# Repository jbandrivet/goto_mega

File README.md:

# GotoAndrivet — Contrôleur Multi-Montures OnStep

**Site du projet : [goto-andrivet.duckdns.org](https://goto-andrivet.duckdns.org)**

Ce projet supporte de manière universelle trois types de montures astronomiques :
1. **Alt-Azimutale (AltAz)** : Pour montures Dobson et Alt-Azimutales standards.
2. **Fourche Équatoriale (ForkEq)** : Pour montures équatoriales à fourche ou tables équatoriales (aucun retournement de méridien requis, suivi sidéral direct sur l'angle horaire).
3. **Monture Équatoriale Allemande (GermanEq / GEM)** : Pour montures équatoriales allemandes (gestion automatique du **retournement de méridien** et de la position de pilier *Pier Side* Est/Ouest).

---

## Installation en un clic (Linux)

La carte du ciel et GoTo (**GotoAndrivet**) et le **configurateur** s'installent ensemble, avec leurs raccourcis sur le Bureau et dans le menu des applications. L'installateur prend toujours la dernière version du dépôt ; ensuite, le bouton « Mise à jour » des applications suffit.

**Ubuntu et Debian, le plus simple : [⬇ Télécharger GotoAndrivet.deb](https://github.com/jbandrivet/goto_mega/releases/latest/download/GotoAndrivet.deb)**

1. Double-cliquez sur le fichier téléchargé : le Centre d'applications s'ouvre. Cliquez sur **Installer** (votre mot de passe est demandé).
2. Ouvrez **GotoAndrivet - Carte du ciel** depuis le menu des applications. La première fois, GotoAndrivet s'installe dans votre dossier personnel (quelques minutes), puis s'ouvre.

**Autres distributions : [⬇ Télécharger l'installateur Linux](https://github.com/jbandrivet/goto_mega/releases/latest/download/Install_Goto_Universal)**, puis, dans le dossier Téléchargements :

1. clic droit sur `Install_Goto_Universal` → **Propriétés** → activez **Exécutable comme programme** ;
2. clic droit → **Exécuter comme un programme**, puis « Installer ».

Le double-clic ne lance pas un programme téléchargé : il propose de chercher une application dans le Centre d'applications, qui ne trouve rien. Passez par le clic droit.

Ou en une seule commande, dans un terminal :

```sh
wget -qO- https://raw.githubusercontent.com/jbandrivet/goto_mega/main/installer.sh | sh
```

Prérequis pour l'installateur et la commande (le paquet .deb les installe tout seul) : `sudo apt install python3-venv python3-tk`. Pour le module caméra : `sudo apt install astrometry.net astrometry-data-tycho2` et le SDK caméra de ZWO.

---

## Structure du Projet

* **`goto_andrivet.py`** : L'application principale en Python (interface graphique Tkinter avec carte du ciel interactive : étoiles, constellations, Soleil, Lune et planètes, catalogues Messier/NGC/IC/Caldwell, dérotateur et mise à jour en ligne).
* **`photo.py`** : Le module caméra de la carte du ciel (caméra ZWO ou simulée, photos FITS, astrométrie locale avec solve-field, correction après GoTo, modèle de pointage, angle de cadrage).
* **`guidage.py`** : Le module de guidage de la carte du ciel (deuxième caméra ZWO ou simulée, calibration automatique, corrections envoyées par le PC à la monture, courbe des erreurs, dithering entre les poses).
* **`goto_andrivet_config_tool.py`** : L'utilitaire de configuration en style Windows 95 permettant de régler les coordonnées, vitesses, rapports d'engrenage et de flasher le firmware.
* **`raquette_virtuelle.py`** : L'émulateur de la raquette Teensy pour piloter le télescope depuis l'ordinateur.
* **`ciel_donnees.py`** : Les données de la carte du ciel : étoiles du Yale Bright Star Catalogue jusqu'à la magnitude 6,5, lignes et noms des 88 constellations (Stellarium, CC BY-SA 4.0), objets Messier, Caldwell, NGC et IC (OpenNGC, CC BY-SA 4.0). Fichier généré par `outils/generer_ciel_donnees.py` : ne pas le modifier à la main.
* **`mise_a_jour.py`** : La mise à jour en ligne depuis GitHub, commune à la carte du ciel et à l'utilitaire de configuration.
* **`outils/`** : Le générateur de `ciel_donnees.py` (il télécharge les catalogues auprès du CDS, de Stellarium et d'OpenNGC).
* **`mega_monture/`** : Le firmware classique (1 étoile) pour le contrôleur Arduino Mega 2560.
* **`teensy_monture/`** : Le nouveau firmware haute performance pour contrôleur Teensy 4.1 (Inclut le Modèle de Pointage N-Étoiles par interpolation IDW).
* **`teensy_raquette/`** : Le firmware C++ pour la raquette physique avec écran LCD (sur Teensy 4.1).

---

## Guide d'Installation & Mode d'Emploi

### 1. Prérequis
Pour exécuter les applications graphiques en Python sur votre ordinateur, vous devez disposer de **Python 3**, du module **Tkinter** et de la bibliothèque **pyserial**. La bibliothèque **ephem** est facultative : elle affiche le Soleil, la Lune et les planètes sur la carte du ciel.

Sur Ubuntu / Debian / Raspberry Pi OS, installez-les via votre terminal :
```bash
sudo apt update
sudo apt install python3 python3-tk python3-pip
pip3 install pyserial ephem
```

### 2. Démarrage des Applications
Exécutez les scripts Python correspondants depuis le dossier du projet :

* **Configuration & Flashage** :
  ```bash
  python3 goto_andrivet_config_tool.py
  ```
* **Cartographie du Ciel & Pilotage** :
  ```bash
  python3 goto_andrivet.py
  ```
* **Raquette Virtuelle (Émulateur)** :
  ```bash
  python3 raquette_virtuelle.py
  ```

### 3. Compiler & Flasher sans IDE Arduino
Vous pouvez programmer vos cartes directement depuis l'utilitaire de configuration (sans avoir besoin d'ouvrir l'IDE Arduino classique) :
1. Installez l'utilitaire [arduino-cli](https://arduino.github.io/arduino-cli/latest/) sur votre PC.
2. Ouvrez l'utilitaire de configuration (`python3 goto_andrivet_config_tool.py`).
3. Sélectionnez le **Port** série de votre carte dans les paramètres de connexion.
4. Dans l'encadré **« Téléversement du Firmware »**, cliquez sur le bouton correspondant à votre carte pour compiler et flasher automatiquement.

### 4. Schéma de Câblage Rapide (Monture : Mega ou Teensy)

Câblez votre contrôleur principal en suivant ce schéma (les broches sont identiques pour le Mega et le Teensy, à l'exception du Buzzer, de l'`ENB` du focuseur et du GPS, dont les fils TX/RX sont croisés d'une carte à l'autre) :

| Composant / Axe | Broche Arduino Mega 2560 | Broche Teensy 4.1 | Signal Module / Driver |
| :--- | :--- | :--- | :--- |
| **Moteur Azimut (AZ/RA)** | **Pin 2** | **Pin 2** | `PUL+` (Pulse/Step) |
| | **Pin 3** | **Pin 3** | `DIR+` (Direction) |
| | **Pin 4** | **Pin 4** | `ENB+` (Enable) |
| **Moteur Altitude (ALT/DEC)** | **Pin 5** | **Pin 5** | `PUL+` (Pulse/Step) |
| | **Pin 6** | **Pin 6** | `DIR+` (Direction) |
| | **Pin 7** | **Pin 7** | `ENB+` (Enable) |
| **Moteur Dérotateur** | **Pin 8** | **Pin 8** | `PUL+` (Pulse/Step) |
| | **Pin 9** | **Pin 9** | `DIR+` (Direction) |
| | **Pin 10** | **Pin 10** | `ENB+` (Enable) |
| **Moteur Focuseur** | **Pin 11** | **Pin 11** | `PUL+` (Pulse/Step) |
| | **Pin 12** | **Pin 12** | `DIR+` (Direction) |
| | **Pin 13** | **Pin 21** | `ENB+` (Enable) |
| **Buzzer** | **Pin 49** | **Pin 20** | Mega : borne `+` en direct (buzzer actif). Teensy : par un transistor (voir § 6) |
| **Port Série PC** | **Non dispo** | **Pin 25 (RX6)** | `TX` de l'adaptateur USB/Série TTL (Câble long) |
| | **Non dispo** | **Pin 24 (TX6)** | `RX` de l'adaptateur USB/Série TTL |
| **Raquette Teensy** | **Pin 15 (RX3)** | **Pin 15 (RX3)** | `TX` de la raquette Teensy |
| | **Pin 14 (TX3)** | **Pin 14 (TX3)** | `RX` de la raquette Teensy |
| **Module GPS** | **Pin 17 (RX2)** | **Pin 16 (RX4)** | `TX` du module GPS |
| | **Pin 16 (TX2)** | **Pin 17 (TX4)** | `RX` du module GPS |
| **Drivers TMC5160 (SPI1, PCB)** | **Non dispo** | **Pin 26 (MOSI1)** | `SDI` des modules (ponts SPI fermés) |
| | **Non dispo** | **Pin 27 (SCK1)** | `SCK` des modules |
| | **Non dispo** | **Pin 39 (MISO1)** | `SDO` des modules |
| | **Non dispo** | **Pins 41 / 40 / 38 / 37** | `CSN` AZ / ALT / Dérotateur / Focuseur |

*Note : Les signaux de masse négatifs (`PUL-`, `DIR-`, `ENB-` des drivers, GND du buzzer, du GPS et de la Teensy) doivent tous être connectés à une broche **GND** de votre carte.*
*(Consultez le fichier `fiche_technique.md` pour des explications approfondies).*

### 4.1 Schéma de Câblage de la Raquette (Teensy 4.1)

Si vous fabriquez la raquette physique avec un Teensy 4.1, voici le câblage à effectuer :

| Composant | Broche Teensy 4.1 | Connexion / Signal |
| :--- | :--- | :--- |
| **Écran LCD (I2C)** | **Pin 18 (SDA0)** | `SDA` de l'écran LCD |
| | **Pin 19 (SCL0)** | `SCL` de l'écran LCD |
| | **VIN** | `VCC` (5V) de l'écran LCD |
| | **GND** | `GND` de l'écran LCD |
| **Boutons Poussoirs** | **Pin 6** | Bouton **Haut (UP)** (vers GND) |
| | **Pin 7** | Bouton **Bas (DOWN)** (vers GND) |
| | **Pin 8** | Bouton **Gauche (LEFT)** (vers GND) |
| | **Pin 9** | Bouton **Droite (RIGHT)** (vers GND) |
| | **Pin 10** | Bouton **Validation (ENTER)** (vers GND) |
| **Câble RJ11 (vers Mega)**| **GND** | Pin 1 RJ11 (`GND` de la Monture) |
| | **VIN** | Pin 2 RJ11 (`VIN` / `5V` de la Monture) |
| | **Pin 1 (TX1)** | Pin 3 RJ11 (vers `RX3` Pin 15 Monture) |
| | **Pin 0 (RX1)** | Pin 4 RJ11 (vers `TX3` Pin 14 Monture) |

*ATTENTION : Le Teensy est alimenté par la pin 5V du Mega via VIN. Ne pas brancher l'USB du Teensy en même temps, sauf si le pad VUSB a été coupé au préalable.*

### 5. Arduino Mega 2560 vs Teensy 4.1 (Contrôleur de Monture)

Le projet vous permet de choisir le cerveau principal de la monture. Bien que le câblage soit quasiment identique, voici les différences pour vous aider à choisir :

| Caractéristique | Arduino Mega 2560 | Teensy 4.1 |
| :--- | :--- | :--- |
| **Vitesse de calcul** | 16 MHz (8-bit) | **600 MHz** (32-bit ARM) |
| **Précision (Maths)** | Flottants 32-bit lents | **Flottants 64-bit (double)** natifs ultra-rapides |
| **Microstepping & Vitesse max**| Limité (saturera à très haut microstepping) | **Parfait** (génère des impulsions à plus de 200kHz sans sourciller) |
| **Modèle de pointage** | Basique | **N-Étoiles** (50 points mémorisés avec calculs IDW) |
| **Evolutivité (Futur)** | Faible | **Très haute** (Port USB Host pour Manette/Gamepad) |
| **Coût** | ~15-20€ (Clones pas chers) | ~35-40€ |

**Recommandation** : Si vous utilisez de petits drivers (1/16 ou 1/32 de pas) et voulez un système économique, le **Mega 2560** fait parfaitement le travail. Si vous utilisez des drivers modernes (TMC2209, M542) à fort microstepping (1/128, 1/256), que vous voulez des déplacements GoTo ultra-rapides et silencieux, et le modèle de pointage multi-étoiles intégré, optez sans hésiter pour le **Teensy 4.1**.

### 6. Matériel Compatible

Pour monter votre système GotoAndrivet, les composants matériels suivants sont compatibles et recommandés :

* **Cartes de Contrôle** :
  * **Arduino Mega 2560** ou **Teensy 4.1** (au choix pour la carte principale de la monture).
  * **Teensy 4.1** (pour la raquette de commande physique - *Optionnelle*).
* **Drivers de Moteurs** :
  * Drivers standard acceptant des entrées `PUL/DIR` (Impulsion/Direction) comme les modèles **M542**, **DM542**, **TB6600**, **TMC2209**, etc.
  * Deux PCB monture (Teensy) au choix : une carte à modules StepStick, dont le **BTT TMC5160 Pro** configuré en SPI, et une carte pour drivers externes (voir *Cartes Monture* plus bas).
* **Moteurs** :
  * Moteurs pas à pas bipolaires (ex. **NEMA 17** ou **NEMA 23** en 200 pas/tour).
* **Module GPS (Optionnel)** :
  * Module **Adafruit Ultimate GPS** (MTK3339) ou tout autre récepteur GPS délivrant des trames NMEA standards à 9600 bauds sur port série.
* **Afficheur Raquette** :
  * Écran **LCD 20x4** caractères équipé d'un adaptateur **I2C** (généralement à l'adresse `0x27`).
* **Boutons Raquette** :
  * 5 boutons poussoirs momentanés (Haut, Bas, Gauche, Droite, Validation).
* **Alerte Sonore** :
  * Un **Buzzer actif 5V** ou un **Buzzer passif**. Sur le Mega, un buzzer actif se câble directement. Sur le Teensy, passez par un transistor : une broche ne fournit que quelques mA, et un buzzer passif en tire 80 à 200. Un NPN (PN2222A) avec 1 kΩ sur la base, le buzzer entre le 5V et le collecteur, en série avec 68 Ω, et une diode 1N4148 à ses bornes : c'est le montage des cartes.

*Note concernant la raquette physique : La construction de la raquette matérielle (carte Teensy, écran LCD et boutons) n'est **pas obligatoire**. Si vous utilisez la monture en mode "remote", ou que vous la pilotez exclusivement depuis un PC, un planétarium, ou un boîtier type ASIAIR, l'Arduino Mega suffit à lui seul pour tout gérer via la connexion USB.*

---

## Fonctionnalités Avancées

* **Modèle de Pointage N-Étoiles (Teensy Monture uniquement)** : Interpolation des erreurs de suivi et de pointage par IDW (Inverse Distance Weighting) jusqu'à 50 étoiles mémorisées. Support de la commande de remise à zéro `:CML#`.
* **Ajout du type de monture `GermanEq`** : Le firmware de l'Arduino Mega calcule automatiquement les inversions d'axes (Ascension Droite et Déclinaison) lors du franchissement du méridien.
* **Commande standard `:Gm#` implémentée** : Renvoie le *Pier Side* (`E#` pour l'Est, `W#` pour l'Ouest, `N#` pour les autres modes) requis pour les logiciels de guidage comme Ekos/INDI.
* **Commande standard `:D#` implémentée** : Permet l'interrogation dynamique du statut de pointage (Slewing), accélérant drastiquement le modèle de pointage automatique ZWO en évitant les pauses fixes.
* **Intégration complète dans les interfaces** : Le sélecteur de monture dans `goto_andrivet_config_tool.py`, `goto_andrivet.py` et la raquette physique Teensy supporte désormais les trois options distinctes (`AltAz`, `ForkEq`, `GermanEq`).

---

## Licence

Ce projet est sous licence **GNU GPL v3**. Consultez le fichier [LICENSE](LICENSE) pour plus de détails.

## Cartes Monture (PCB 36V / 12V)

Il existe deux cartes monture, au choix selon les drivers utilisés. Elles ont les mêmes dimensions (150 × 110 mm), les mêmes fixations, les mêmes connecteurs d'alimentation, de raquette, de GPS et de PC, et le même câblage du Teensy : le firmware est identique.

| Carte | Dossier | Drivers | Boîtier |
|---|---|---|---|
| **StepStick** | `pcb/monture/` | 4 modules au format StepStick sur la carte (A4988, DRV8825, TMC2208/2209, TMC5160 en SPI) | `boitier_monture.scad`, 45 mm de haut |
| **Drivers externes** | `pcb/monture_ext/` | 4 drivers externes (DM542, DM556, TB6600…), signaux 5 V et alimentation par axe | `boitier_monture_ext.scad`, 35 mm de haut |

Sans PCB, câblez vous-même le Mega ou le Teensy en suivant le plan de câblage de la section 4. Dans l'outil de configuration, indiquez votre choix sur la ligne **« Câblage monture »** (PCB StepStick, PCB drivers externes ou câblage manuel). Avec un PCB, l'outil impose le Teensy 4.1, et la section TMC5160 n'est active qu'avec la carte StepStick. Le bouton **« Plan de câblage »** affiche les broches de la carte choisie et les connecteurs du PCB.

### Commun aux deux cartes
- **Alimentation** : un seul bus moteur, alimenté soit par le **bornier 36V**, soit par la **prise jack 12V**. Chaque entrée passe par une des deux diodes Schottky de `D_IN` (MBR20100CT, cathode commune) : des fils inversés ou un jack à centre négatif ne passent pas, et le 36V du bornier ne remonte pas dans le bloc 12V. Vient ensuite le fusible `F_IN` (TR5 temporisé 4 A, sur support), commun aux deux entrées. Toute la carte et tous les drivers reçoivent la tension de l'entrée branchée, moins environ 0,5 V.
  - En 36V, n'utilisez pas d'A4988 (35 V max) ni de TMC2208/TMC2209 (29 V max) : pour ces petits drivers, alimentez la carte uniquement par le jack 12V.
- Le buck LM2596HV (jusqu'à 60 V en entrée) fabrique le 5V à partir de 12V comme de 36V.
- Des résistances de rappel (`RN_EN`) maintiennent EN à l'état haut tant que le Teensy n'a pas démarré : les drivers restent désactivés à la mise sous tension.
- Le Teensy 4.1 de la monture n'a pas de port USB Host câblé.
- Sur le Teensy de la monture, **coupez le pont VUSB-VIN** sous la carte : le Teensy est alimenté par le 5V du PCB (VIN) et reste branché en USB au PC.
- Port **PC SERIAL** (Serial6, broches 24/25) : les repères RX/TX sont donnés côté Teensy (`3 TX6`, `4 RX6`). Il faut donc les croiser vers l'adaptateur, et ne pas brancher son 5V sur la broche `2 +5V`. L'adaptateur USB-série doit travailler en **3,3 V** : un adaptateur 5 V enverrait 5 V sur `RX6`, que le Teensy ne supporte pas.
- Le buzzer est commandé par un transistor (`Q_BUZ`, PN2222A) et alimenté en 5V à travers 68 Ω, avec une diode 1N4148 à ses bornes : un buzzer actif 5V ou un buzzer passif conviennent.

### Carte StepStick (`pcb/monture/`)
- Chaque axe a un support au format **StepStick / Pololu** (2 × 8 broches espacées de 12,7 mm), piloté directement par le Teensy, et un bornier moteur à 4 points (bobine 1 : 1B/1A, bobine 2 : 2A/2B).
- Orientation d'un module StepStick : sa broche **EN** va sur la pastille marquée `EN` (en haut à gauche). **VMOT** se trouve donc en face, sur la pastille marquée `VM`. La logique des modules (VIO) est alimentée en **3,3 V**.
- **Ponts SPI (TMC5160)** : sous chaque support, entre les deux rangées, se trouvent 5 ponts à souder marqués `SPI`. Ils sont en face des broches 2 à 6 du module. De haut en bas : `SDI` vers MOSI1 (broche 26), `SCK` vers SCK1 (27), `CSN` vers le CS de l'axe (41 AZ, 40 ALT, 38 dérotateur, 37 focuseur), `SDO` vers MISO1 (39), et `CLK` vers GND (horloge interne du TMC5160).
  - **Ponts ouverts** (réglage par défaut) : le support accepte les modules STEP/DIR sans SPI, c'est-à-dire TMC2208/TMC2209 en mode autonome, A4988 ou DRV8825.
    - **A4988 et DRV8825 : reliez RESET à SLEEP sur le module** (petit fil ou goutte d'étain entre les deux broches voisines). Le PCB laisse ces broches en l'air : sans ce pont, l'A4988 a un RESET flottant, et le DRV8825, dont RESET a un rappel interne au niveau bas, ne bouge pas du tout.
    - **Micro-pas** : le PCB ne câble pas les broches MS1 à MS3. Elles restent au niveau bas, ce qui donne le pas entier sur un A4988 ou un DRV8825 et 1/8 de pas sur un TMC2208/TMC2209. Pour une autre valeur, reliez les broches MSx voulues à la broche VIO du support (3,3 V) par un fil soudé sur le module, d'après sa table de micro-pas. Le réglage *Microstepping* de l'outil de configuration doit toujours être égal aux micro-pas du module (1, 8, 16…).
  - **Les 5 ponts fermés** (une goutte d'étain chacun) : pour un **BTT TMC5160 Pro**, ou un autre TMC5160 au format StepStick avec le même brochage (EN, SDI, SCK, CSN, SDO, CLK, STEP, DIR).
  - Ne fermez jamais les ponts avec un A4988, un DRV8825 ou un TMC2209 : leurs broches MSx, RESET et SLEEP se retrouveraient sur le bus SPI.
- **Configuration des TMC5160 (firmware Teensy)** : au démarrage, puis chaque seconde, le firmware cherche un TMC5160 sur chaque axe et le configure (courant, micro-pas, stealthChop). Un TMC5160 en SPI garde son étage de puissance coupé tant qu'il n'est pas configuré. Si le 36V n'est pas encore là, le module ne répond pas : il est configuré dès que le 36V arrive, et reconfiguré après une coupure.
  - Micro-pas : AZ/ALT utilisent le réglage *Microstepping*, qui doit être une puissance de 2 (16, 32, 64, 128 ou 256). Une valeur comme 125 est refusée et l'axe reste coupé (état `M`). Le dérotateur et le focuseur sont à 16 micro-pas par défaut : ajustez les *Pas/Deg* du dérotateur en conséquence.
  - Courant : il se règle dans l'outil de configuration, de 100 à 3000 mA RMS par axe (Rsense 0,075 Ω du BTT TMC5160 Pro), avec un courant de maintien en %. Valeurs par défaut : 800 mA pour AZ/ALT, 400 mA pour le dérotateur et le focuseur, maintien à 50 %.
  - Commandes : `:XFS0#` / `:XFS1#` (désactiver / activer, activé par défaut), `:XTS#` (état par axe : `-` SPI désactivé, `0` absent, `1` configuré, `M` micro-pas refusé, `E` défaut driver), `:XTI<a|e|d|f>[mA]#` (courant), `:XTH[%]#` (maintien), `:XTP[0|1]#` (stealthChop), `:XTMd[n]#` / `:XTMf[n]#` (micro-pas dérotateur / focuseur), `:XTC#` (tout reconfigurer). Sans valeur, ces commandes renvoient le réglage en cours.
  - Le firmware Mega n'a pas de SPI : le PCB est prévu pour le Teensy.
  - Hauteur : un TMC5160 avec radiateur est plus haut qu'un StepStick ordinaire. Le boîtier fait donc 45 mm de haut (`box_h` dans `boitier_monture.scad`), ce qui laisse 25,8 mm entre la carte du module et le couvercle. Un BTT TMC5160 Pro (23,2 mm hors tout) passe avec au moins 4 mm de marge, et les grilles du couvercle se trouvent au-dessus des radiateurs.

### Carte drivers externes (`pcb/monture_ext/`)
- Chaque axe a deux borniers sur le bord haut :
  - **`J_VM`** (5,08 mm, fil de 1,5 mm²) : `VM` et `GND`, l'alimentation du driver. `VM` est le bus moteur, donc 36V ou 12V selon l'entrée branchée. Chaque sortie a son condensateur de 220 µF.
  - **`J_SIG`** (3,5 mm) : `EN`, `STEP`, `DIR`, `GND`, en 5 V. Les signaux du Teensy passent par trois 74ACT125, toujours actifs.
- Câblage d'un DM542 (cathode commune) : `STEP` → `PUL+`, `DIR` → `DIR+`, `EN` → `ENA+`, et `GND` → `PUL−`, `DIR−` et `ENA−` reliés ensemble. Le moteur se branche sur le driver. Avec `ENA` câblé, le driver relâche le moteur au parking ; sinon, le moteur reste alimenté en permanence.
- Un plan de cuivre GND (face dessous) et un plan +36V (face dessus, de l'entrée jusqu'aux borniers `J_VM`) portent le courant des drivers.
- Réglages : le *Microstepping* de l'outil de configuration doit être égal au nombre de pas par tour réglé sur le driver divisé par 200 (par exemple 128 pour 25 600 pas/tour). Toutes les valeurs sont acceptées, puissances de 2 ou non. AZ et ALT partagent ce réglage : réglez leurs deux drivers pareil.
- Vitesse de GoTo : le DM542 accepte 200 kHz au plus, avec des impulsions d'au moins 2,5 µs. Restez sous environ 150 kHz, soit une vitesse maximale d'environ 150 000 divisé par le nombre de pas par degré (environ 2,8°/s à 25 600 pas/tour avec une réduction de 750:1).
- Cette carte n'a pas de bus SPI : dans l'outil de configuration, l'état TMC5160 des axes est « absent », ce qui est normal. On peut décocher « Drivers TMC5160 ».

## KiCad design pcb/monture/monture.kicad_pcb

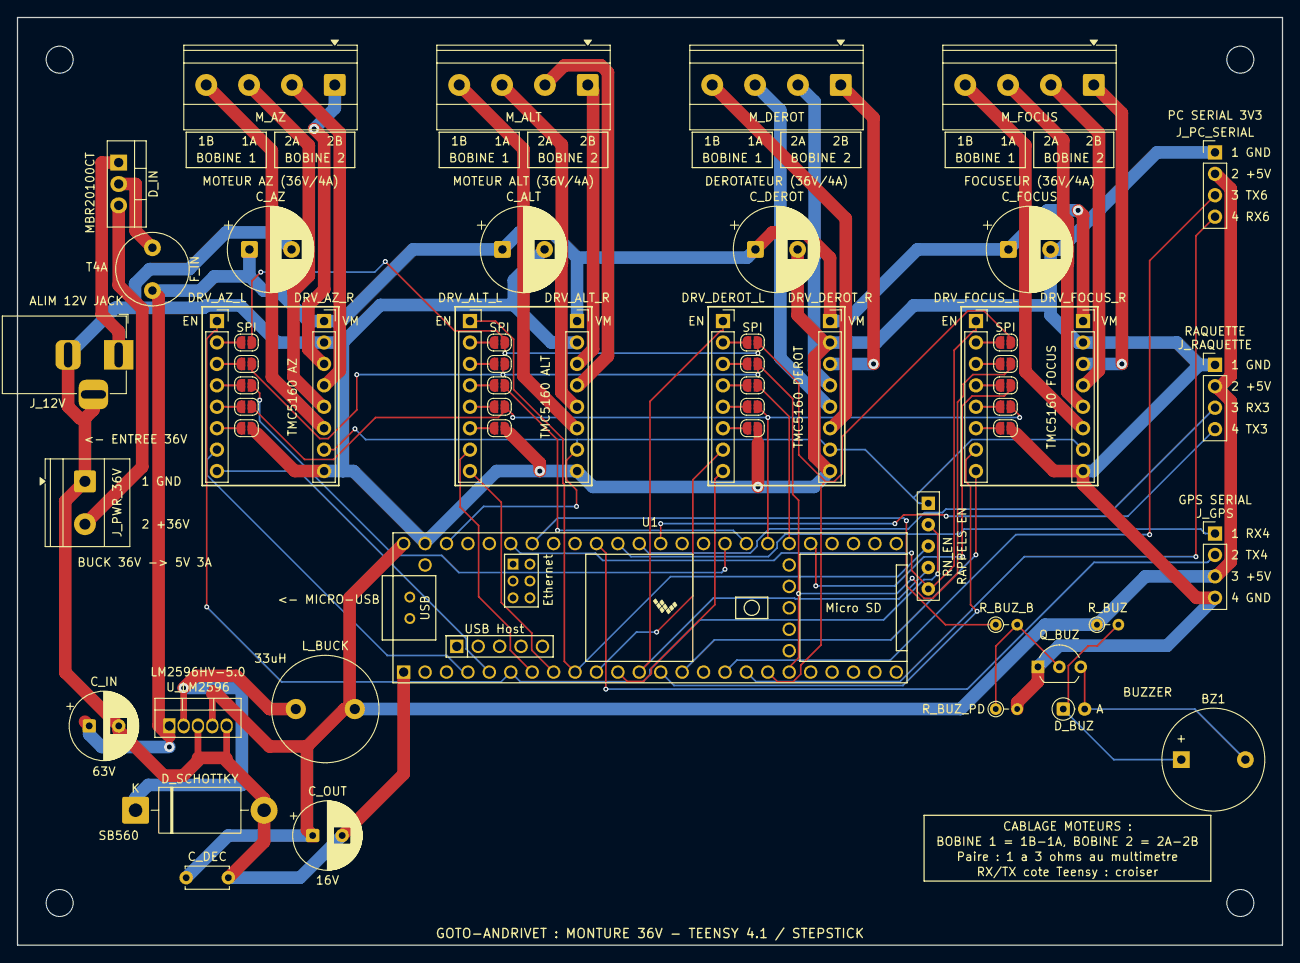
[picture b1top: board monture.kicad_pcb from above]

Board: 2 copper layers, 150.0 x 110.0 mm, 61 parts (0 on the bottom side), 73 nets.

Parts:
BZ1: Buzzer; Buzzer_12x9.5RM7.6
C_ALT: 220uF 63V; CP_Radial_D10.0mm_P5.00mm
C_AZ: 220uF 63V; CP_Radial_D10.0mm_P5.00mm
C_DEC: 100nF; C_Disc_D5.0mm_W2.5mm_P5.00mm
C_DEROT: 220uF 63V; CP_Radial_D10.0mm_P5.00mm
C_FOCUS: 220uF 63V; CP_Radial_D10.0mm_P5.00mm
C_IN: 100uF 63V; CP_Radial_D8.0mm_P3.50mm
C_OUT: 220uF 16V; CP_Radial_D8.0mm_P3.50mm
DRV_ALT_L: Logique; PinSocket_1x08_P2.54mm_Vertical
DRV_ALT_R: Puissance; PinSocket_1x08_P2.54mm_Vertical
DRV_AZ_L: Logique; PinSocket_1x08_P2.54mm_Vertical
DRV_AZ_R: Puissance; PinSocket_1x08_P2.54mm_Vertical
DRV_DEROT_L: Logique; PinSocket_1x08_P2.54mm_Vertical
DRV_DEROT_R: Puissance; PinSocket_1x08_P2.54mm_Vertical
DRV_FOCUS_L: Logique; PinSocket_1x08_P2.54mm_Vertical
DRV_FOCUS_R: Puissance; PinSocket_1x08_P2.54mm_Vertical
D_BUZ: 1N4148; D_DO-35_SOD27_P2.54mm_Vertical_AnodeUp
D_IN: MBR20100CT; TO-220-3_Vertical
D_SCHOTTKY: SB560 (60V 5A); D_DO-201AD_P15.24mm_Horizontal
F_IN: T4A (TR5); Fuse_Littelfuse_372_D8.50mm
H1, H2, H3, H4: M3 Fixation; MountingHole_3.2mm_M3
JP_ALT_CLK: SPI; SolderJumper-2_P1.3mm_Open_RoundedPad1.0x1.5mm
JP_ALT_CSN: SPI; SolderJumper-2_P1.3mm_Open_RoundedPad1.0x1.5mm
JP_ALT_SCK: SPI; SolderJumper-2_P1.3mm_Open_RoundedPad1.0x1.5mm
JP_ALT_SDI: SPI; SolderJumper-2_P1.3mm_Open_RoundedPad1.0x1.5mm
JP_ALT_SDO: SPI; SolderJumper-2_P1.3mm_Open_RoundedPad1.0x1.5mm
JP_AZ_CLK: SPI; SolderJumper-2_P1.3mm_Open_RoundedPad1.0x1.5mm
JP_AZ_CSN: SPI; SolderJumper-2_P1.3mm_Open_RoundedPad1.0x1.5mm
JP_AZ_SCK: SPI; SolderJumper-2_P1.3mm_Open_RoundedPad1.0x1.5mm
JP_AZ_SDI: SPI; SolderJumper-2_P1.3mm_Open_RoundedPad1.0x1.5mm
JP_AZ_SDO: SPI; SolderJumper-2_P1.3mm_Open_RoundedPad1.0x1.5mm
JP_DEROT_CLK: SPI; SolderJumper-2_P1.3mm_Open_RoundedPad1.0x1.5mm
JP_DEROT_CSN: SPI; SolderJumper-2_P1.3mm_Open_RoundedPad1.0x1.5mm
JP_DEROT_SCK: SPI; SolderJumper-2_P1.3mm_Open_RoundedPad1.0x1.5mm
JP_DEROT_SDI: SPI; SolderJumper-2_P1.3mm_Open_RoundedPad1.0x1.5mm
JP_DEROT_SDO: SPI; SolderJumper-2_P1.3mm_Open_RoundedPad1.0x1.5mm
JP_FOCUS_CLK: SPI; SolderJumper-2_P1.3mm_Open_RoundedPad1.0x1.5mm
JP_FOCUS_CSN: SPI; SolderJumper-2_P1.3mm_Open_RoundedPad1.0x1.5mm
JP_FOCUS_SCK: SPI; SolderJumper-2_P1.3mm_Open_RoundedPad1.0x1.5mm
JP_FOCUS_SDI: SPI; SolderJumper-2_P1.3mm_Open_RoundedPad1.0x1.5mm
JP_FOCUS_SDO: SPI; SolderJumper-2_P1.3mm_Open_RoundedPad1.0x1.5mm
J_12V: 12V Jack; BarrelJack_Horizontal
J_GPS: GPS SERIAL4; PinHeader_1x04_P2.54mm_Vertical
J_PC_SERIAL: PC SERIAL6; PinHeader_1x04_P2.54mm_Vertical
J_PWR_36V: ALIM 36V DC; TerminalBlock_Phoenix_MKDS-1,5-2-5.08_1x02_P5.08mm_Horizont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
J_RAQUETTE: VERS RAQUETTE; PinHeader_1x04_P2.54mm_Vertical
L_BUCK: 33uH 3A; L_Radial_D12.5mm_P7.00mm_Fastron_09HCP
M_ALT: MOTEUR ALT; TerminalBlock_Phoenix_MKDS-1,5-4-5.08_1x04_P5.08mm_Horizont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
M_AZ: MOTEUR AZ; TerminalBlock_Phoenix_MKDS-1,5-4-5.08_1x04_P5.08mm_Horizont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
M_DEROT: MOTEUR DEROT; TerminalBlock_Phoenix_MKDS-1,5-4-5.08_1x04_P5.08mm_Horizont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
M_FOCUS: MOTEUR FOCUS; TerminalBlock_Phoenix_MKDS-1,5-4-5.08_1x04_P5.08mm_Horizont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
Q_BUZ: PN2222A; TO-92_Inline_Wide
RN_EN: 10k x4 (commun broche 1); R_Array_SIP5
R_BUZ: 68; R_Axial_DIN0204_L3.6mm_D1.6mm_P2.54mm_Vertical
R_BUZ_B: 1k; R_Axial_DIN0204_L3.6mm_D1.6mm_P2.54mm_Vertical
R_BUZ_PD: 10k; R_Axial_DIN0204_L3.6mm_D1.6mm_P2.54mm_Vertical
U1: Teensy 4.1; Teensy41
U_LM2596: LM2596HVT-5.0; TO-220-5_Vertical

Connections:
+3V3: DRV_ALT_R.7, DRV_AZ_R.7, DRV_DEROT_R.7, DRV_FOCUS_R.7, RN_EN.1, U1.46
+5V: C_DEC.1, C_OUT.1, J_GPS.3, J_PC_SERIAL.2, J_RAQUETTE.2, L_BUCK.2, R_BUZ.1, U1.48, U_LM2596.4
+36V: C_ALT.1, C_AZ.1, C_DEROT.1, C_FOCUS.1, C_IN.1, DRV_ALT_R.1, DRV_AZ_R.1, DRV_DEROT_R.1, DRV_FOCUS_R.1, F_IN.2, U_LM2596.1
ALT_1A: DRV_ALT_R.5, M_ALT.3
ALT_1B: DRV_ALT_R.6, M_ALT.4
ALT_2A: DRV_ALT_R.4, M_ALT.2
ALT_2B: DRV_ALT_R.3, M_ALT.1
ALT_CLK: DRV_ALT_L.6, JP_ALT_CLK.1
ALT_CSN: DRV_ALT_L.4, JP_ALT_CSN.1
ALT_DIR: DRV_ALT_L.8, U1.8
ALT_EN: DRV_ALT_L.1, RN_EN.3, U1.9
ALT_SCK: DRV_ALT_L.3, JP_ALT_SCK.1
ALT_SDI: DRV_ALT_L.2, JP_ALT_SDI.1
ALT_SDO: DRV_ALT_L.5, JP_ALT_SDO.1
ALT_STEP: DRV_ALT_L.7, U1.7
AZ_1A: DRV_AZ_R.5, M_AZ.3
AZ_1B: DRV_AZ_R.6, M_AZ.4
AZ_2A: DRV_AZ_R.4, M_AZ.2
AZ_2B: DRV_AZ_R.3, M_AZ.1
AZ_CLK: DRV_AZ_L.6, JP_AZ_CLK.1
AZ_CSN: DRV_AZ_L.4, JP_AZ_CSN.1
AZ_DIR: DRV_AZ_L.8, U1.5
AZ_EN: DRV_AZ_L.1, RN_EN.2, U1.6
AZ_SCK: DRV_AZ_L.3, JP_AZ_SCK.1
AZ_SDI: DRV_AZ_L.2, JP_AZ_SDI.1
AZ_SDO: DRV_AZ_L.5, JP_AZ_SDO.1
AZ_STEP: DRV_AZ_L.7, U1.4
BUZZER: R_BUZ_B.1, U1.42
BUZ_A: BZ1.1, D_BUZ.1, R_BUZ.2
BUZ_B: Q_BUZ.2, R_BUZ_B.2, R_BUZ_PD.1
BUZ_C: BZ1.2, D_BUZ.2, Q_BUZ.3
DEROT_1A: DRV_DEROT_R.5, M_DEROT.3
DEROT_1B: DRV_DEROT_R.6, M_DEROT.4
DEROT_2A: DRV_DEROT_R.4, M_DEROT.2
DEROT_2B: DRV_DEROT_R.3, M_DEROT.1
DEROT_CLK: DRV_DEROT_L.6, JP_DEROT_CLK.1
DEROT_CSN: DRV_DEROT_L.4, JP_DEROT_CSN.1
DEROT_DIR: DRV_DEROT_L.8, U1.11
DEROT_EN: DRV_DEROT_L.1, RN_EN.4, U1.12
DEROT_SCK: DRV_DEROT_L.3, JP_DEROT_SCK.1
DEROT_SDI: DRV_DEROT_L.2, JP_DEROT_SDI.1
DEROT_SDO: DRV_DEROT_L.5, JP_DEROT_SDO.1
DEROT_STEP: DRV_DEROT_L.7, U1.10
FOCUS_1A: DRV_FOCUS_R.5, M_FOCUS.3
FOCUS_1B: DRV_FOCUS_R.6, M_FOCUS.4
FOCUS_2A: DRV_FOCUS_R.4, M_FOCUS.2
FOCUS_2B: DRV_FOCUS_R.3, M_FOCUS.1
FOCUS_CLK: DRV_FOCUS_L.6, JP_FOCUS_CLK.1
FOCUS_CSN: DRV_FOCUS_L.4, JP_FOCUS_CSN.1
FOCUS_DIR: DRV_FOCUS_L.8, U1.14
FOCUS_EN: DRV_FOCUS_L.1, RN_EN.5, U1.43
FOCUS_SCK: DRV_FOCUS_L.3, JP_FOCUS_SCK.1
FOCUS_SDI: DRV_FOCUS_L.2, JP_FOCUS_SDI.1
FOCUS_SDO: DRV_FOCUS_L.5, JP_FOCUS_SDO.1
FOCUS_STEP: DRV_FOCUS_L.7, U1.13
GND: C_ALT.2, C_AZ.2, C_DEC.2, C_DEROT.2, C_FOCUS.2, C_IN.2, C_OUT.2, DRV_ALT_R.2, DRV_ALT_R.8, DRV_AZ_R.2, DRV_AZ_R.8, DRV_DEROT_R.2, DRV_DEROT_R.8, DRV_FOCUS_R.2, DRV_FOCUS_R.8, D_SCHOTTKY.2, JP_ALT_CLK.2, JP_AZ_CLK.2, JP_DEROT_CLK.2, JP_FOCUS_CLK.2, J_12V.2, J_12V.3, J_GPS.4, J_PC_SERIAL.1, J_PWR_36V.1, J_RAQUETTE.1, Q_BUZ.1, R_BUZ_PD.2, U1.1, U1.47, U_LM2596.3, U_LM2596.5
GPS_RX: J_GPS.1, U1.38
GPS_TX: J_GPS.2, U1.39
JACK_IN: D_IN.1, J_12V.1
PC_RX: J_PC_SERIAL.3, U1.16
PC_TX: J_PC_SERIAL.4, U1.17
PWR_IN: D_IN.3, J_PWR_36V.2
RAQUETTE_RX: J_RAQUETTE.3, U1.37
RAQUETTE_TX: J_RAQUETTE.4, U1.36
SPI_CS_ALT: JP_ALT_CSN.2, U1.32
SPI_CS_AZ: JP_AZ_CSN.2, U1.33
SPI_CS_DEROT: JP_DEROT_CSN.2, U1.30
SPI_CS_FOCUS: JP_FOCUS_CSN.2, U1.29
SPI_MISO: JP_ALT_SDO.2, JP_AZ_SDO.2, JP_DEROT_SDO.2, JP_FOCUS_SDO.2, U1.31
SPI_MOSI: JP_ALT_SDI.2, JP_AZ_SDI.2, JP_DEROT_SDI.2, JP_FOCUS_SDI.2, U1.18
SPI_SCK: JP_ALT_SCK.2, JP_AZ_SCK.2, JP_DEROT_SCK.2, JP_FOCUS_SCK.2, U1.19
SW_NODE: D_SCHOTTKY.1, L_BUCK.1, U_LM2596.2
VIN_OR: D_IN.2, F_IN.1

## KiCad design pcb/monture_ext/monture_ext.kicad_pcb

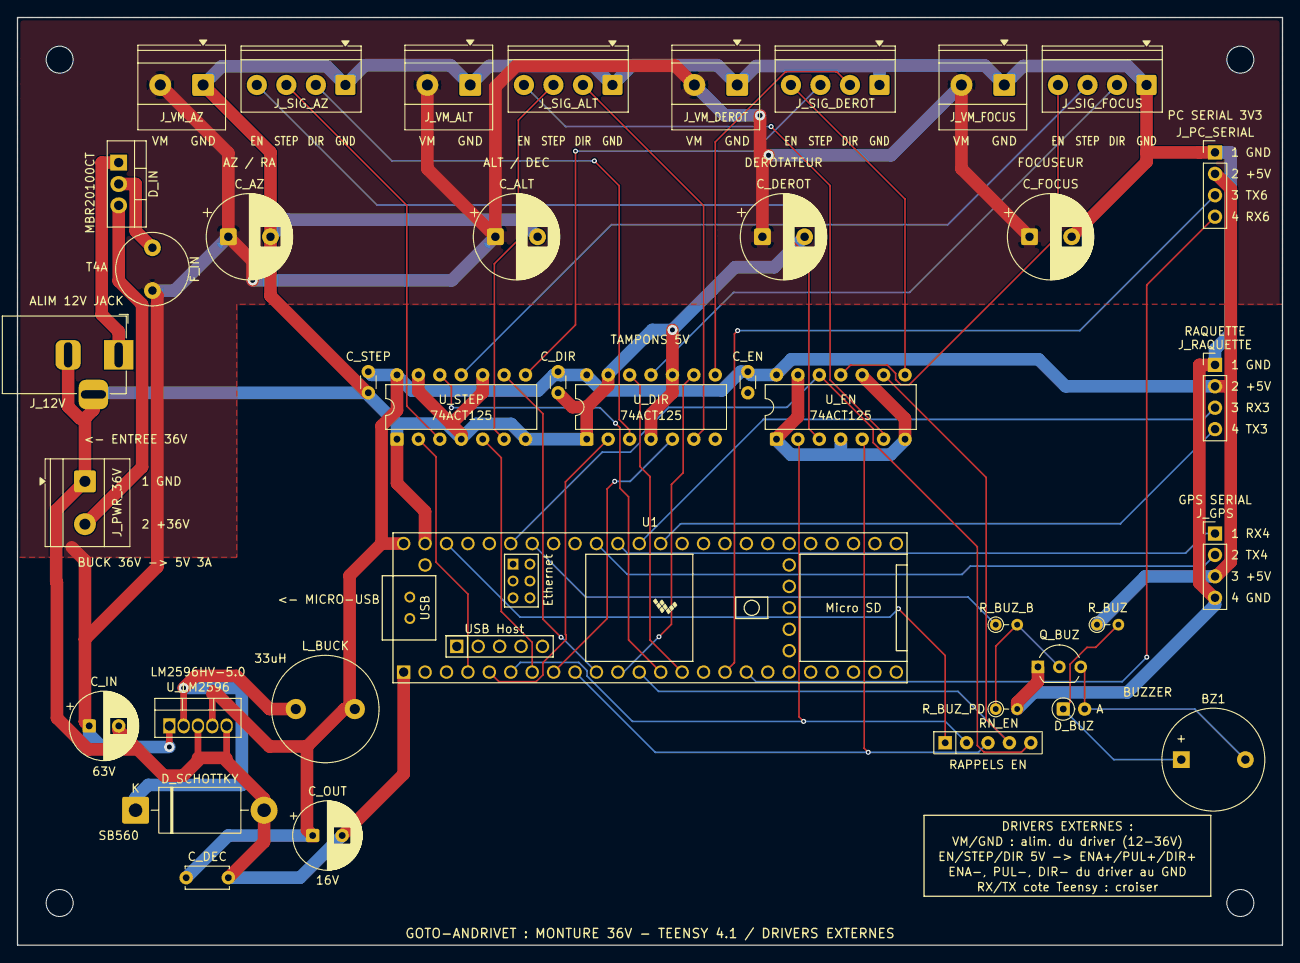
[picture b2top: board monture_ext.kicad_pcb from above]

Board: 2 copper layers, 150.0 x 110.0 mm, 43 parts (0 on the bottom side), 42 nets.

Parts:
BZ1: Buzzer; Buzzer_12x9.5RM7.6
C_ALT: 220uF 63V; CP_Radial_D10.0mm_P5.00mm
C_AZ: 220uF 63V; CP_Radial_D10.0mm_P5.00mm
C_DEC: 100nF; C_Disc_D5.0mm_W2.5mm_P5.00mm
C_DEROT: 220uF 63V; CP_Radial_D10.0mm_P5.00mm
C_DIR: 100nF; C_Disc_D3.0mm_W1.6mm_P2.50mm
C_EN: 100nF; C_Disc_D3.0mm_W1.6mm_P2.50mm
C_FOCUS: 220uF 63V; CP_Radial_D10.0mm_P5.00mm
C_IN: 100uF 63V; CP_Radial_D8.0mm_P3.50mm
C_OUT: 220uF 16V; CP_Radial_D8.0mm_P3.50mm
C_STEP: 100nF; C_Disc_D3.0mm_W1.6mm_P2.50mm
D_BUZ: 1N4148; D_DO-35_SOD27_P2.54mm_Vertical_AnodeUp
D_IN: MBR20100CT; TO-220-3_Vertical
D_SCHOTTKY: SB560 (60V 5A); D_DO-201AD_P15.24mm_Horizontal
F_IN: T4A (TR5); Fuse_Littelfuse_372_D8.50mm
H1, H2, H3, H4: M3 Fixation; MountingHole_3.2mm_M3
J_12V: 12V Jack; BarrelJack_Horizontal
J_GPS: GPS SERIAL4; PinHeader_1x04_P2.54mm_Vertical
J_PC_SERIAL: PC SERIAL6; PinHeader_1x04_P2.54mm_Vertical
J_PWR_36V: ALIM 36V DC; TerminalBlock_Phoenix_MKDS-1,5-2-5.08_1x02_P5.08mm_Horizont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
J_RAQUETTE: VERS RAQUETTE; PinHeader_1x04_P2.54mm_Vertical
J_SIG_ALT: SIGNAUX ALT 5V; TerminalBlock_Phoenix_PT-1,5-4-3.5-H_1x04_P3.50mm_Horizontal
J_SIG_AZ: SIGNAUX AZ 5V; TerminalBlock_Phoenix_PT-1,5-4-3.5-H_1x04_P3.50mm_Horizontal
J_SIG_DEROT: SIGNAUX DEROT 5V; TerminalBlock_Phoenix_PT-1,5-4-3.5-H_1x04_P3.50mm_Horizontal
J_SIG_FOCUS: SIGNAUX FOCUS 5V; TerminalBlock_Phoenix_PT-1,5-4-3.5-H_1x04_P3.50mm_Horizontal
J_VM_ALT: ALIM DRIVER ALT; TerminalBlock_Phoenix_MKDS-1,5-2-5.08_1x02_P5.08mm_Horizont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
J_VM_AZ: ALIM DRIVER AZ; TerminalBlock_Phoenix_MKDS-1,5-2-5.08_1x02_P5.08mm_Horizont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
J_VM_DEROT: ALIM DRIVER DEROT; TerminalBlock_Phoenix_MKDS-1,5-2-5.08_1x02_P5.08mm_Horizont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
J_VM_FOCUS: ALIM DRIVER FOCUS; TerminalBlock_Phoenix_MKDS-1,5-2-5.08_1x02_P5.08mm_Horizont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
L_BUCK: 33uH 3A; L_Radial_D12.5mm_P7.00mm_Fastron_09HCP
Q_BUZ: PN2222A; TO-92_Inline_Wide
RN_EN: 10k x4 (commun broche 1); R_Array_SIP5
R_BUZ: 68; R_Axial_DIN0204_L3.6mm_D1.6mm_P2.54mm_Vertical
R_BUZ_B: 1k; R_Axial_DIN0204_L3.6mm_D1.6mm_P2.54mm_Vertical
R_BUZ_PD: 10k; R_Axial_DIN0204_L3.6mm_D1.6mm_P2.54mm_Vertical
U1: Teensy 4.1; Teensy41
U_DIR: 74ACT125; DIP-14_W7.62mm
U_EN: 74ACT125; DIP-14_W7.62mm
U_LM2596: LM2596HVT-5.0; TO-220-5_Vertical
U_STEP: 74ACT125; DIP-14_W7.62mm

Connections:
+3V3: RN_EN.1, U1.46
+5V: C_DEC.1, C_DIR.2, C_EN.2, C_OUT.1, C_STEP.2, J_GPS.3, J_PC_SERIAL.2, J_RAQUETTE.2, L_BUCK.2, R_BUZ.1, U1.48, U_DIR.14, U_EN.14, U_LM2596.4, U_STEP.14
+36V: C_ALT.1, C_AZ.1, C_DEROT.1, C_FOCUS.1, C_IN.1, F_IN.2, J_VM_ALT.2, J_VM_AZ.2, J_VM_DEROT.2, J_VM_FOCUS.2, U_LM2596.1
ALT_DIR: U1.8, U_DIR.5
ALT_DIR_EXT: J_SIG_ALT.2, U_DIR.6
ALT_EN: RN_EN.3, U1.9, U_EN.5
ALT_EN_EXT: J_SIG_ALT.4, U_EN.6
ALT_STEP: U1.7, U_STEP.5
ALT_STEP_EXT: J_SIG_ALT.3, U_STEP.6
AZ_DIR: U1.5, U_DIR.2
AZ_DIR_EXT: J_SIG_AZ.2, U_DIR.3
AZ_EN: RN_EN.2, U1.6, U_EN.2
AZ_EN_EXT: J_SIG_AZ.4, U_EN.3
AZ_STEP: U1.4, U_STEP.2
AZ_STEP_EXT: J_SIG_AZ.3, U_STEP.3
BUZZER: R_BUZ_B.1, U1.42
BUZ_A: BZ1.1, D_BUZ.1, R_BUZ.2
BUZ_B: Q_BUZ.2, R_BUZ_B.2, R_BUZ_PD.1
BUZ_C: BZ1.2, D_BUZ.2, Q_BUZ.3
DEROT_DIR: U1.11, U_DIR.9
DEROT_DIR_EXT: J_SIG_DEROT.2, U_DIR.8
DEROT_EN: RN_EN.4, U1.12, U_EN.9
DEROT_EN_EXT: J_SIG_DEROT.4, U_EN.8
DEROT_STEP: U1.10, U_STEP.9
DEROT_STEP_EXT: J_SIG_DEROT.3, U_STEP.8
FOCUS_DIR: U1.14, U_DIR.12
FOCUS_DIR_EXT: J_SIG_FOCUS.2, U_DIR.11
FOCUS_EN: RN_EN.5, U1.43, U_EN.12
FOCUS_EN_EXT: J_SIG_FOCUS.4, U_EN.11
FOCUS_STEP: U1.13, U_STEP.12
FOCUS_STEP_EXT: J_SIG_FOCUS.3, U_STEP.11
GND: C_ALT.2, C_AZ.2, C_DEC.2, C_DEROT.2, C_DIR.1, C_EN.1, C_FOCUS.2, C_IN.2, C_OUT.2, C_STEP.1, D_SCHOTTKY.2, J_12V.2, J_12V.3, J_GPS.4, J_PC_SERIAL.1, J_PWR_36V.1, J_RAQUETTE.1, J_SIG_ALT.1, J_SIG_AZ.1, J_SIG_DEROT.1, J_SIG_FOCUS.1, J_VM_ALT.1, J_VM_AZ.1, J_VM_DEROT.1, J_VM_FOCUS.1, Q_BUZ.1, R_BUZ_PD.2, U1.1, U1.47, U_DIR.1, U_DIR.4, U_DIR.7, U_DIR.10, U_DIR.13, U_EN.1, U_EN.4, U_EN.7, U_EN.10, U_EN.13, U_LM2596.3, U_LM2596.5, U_STEP.1, U_STEP.4, U_STEP.7, U_STEP.10, U_STEP.13
GPS_RX: J_GPS.1, U1.38
GPS_TX: J_GPS.2, U1.39
JACK_IN: D_IN.1, J_12V.1
PC_RX: J_PC_SERIAL.3, U1.16
PC_TX: J_PC_SERIAL.4, U1.17
PWR_IN: D_IN.3, J_PWR_36V.2
RAQUETTE_RX: J_RAQUETTE.3, U1.37
RAQUETTE_TX: J_RAQUETTE.4, U1.36
SW_NODE: D_SCHOTTKY.1, L_BUCK.1, U_LM2596.2
VIN_OR: D_IN.2, F_IN.1

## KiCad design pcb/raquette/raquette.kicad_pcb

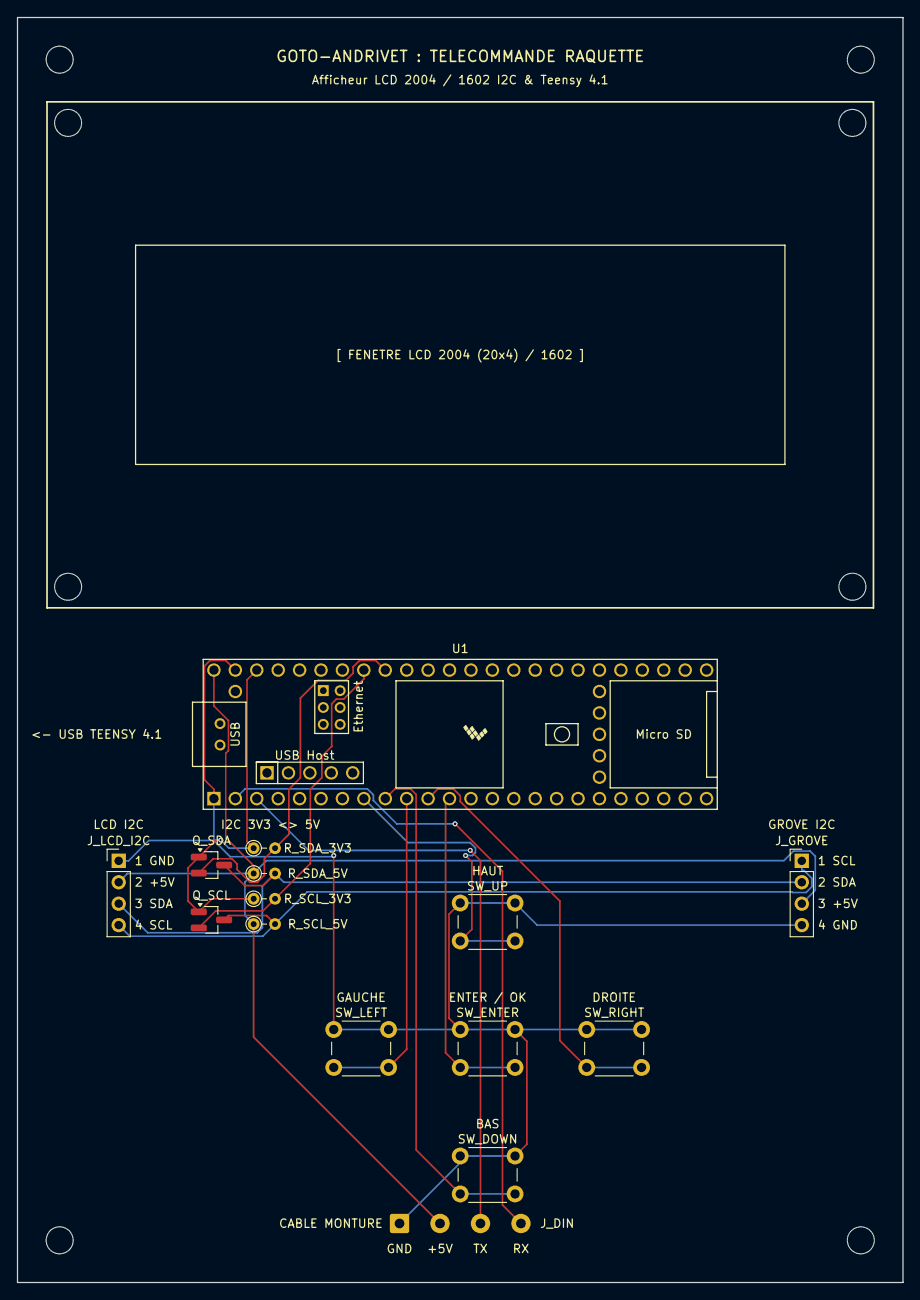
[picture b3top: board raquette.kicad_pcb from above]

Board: 2 copper layers, 105.0 x 150.0 mm, 23 parts (0 on the bottom side), 14 nets.

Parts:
H1, H2, H3, H4: M3 Fixation; MountingHole_3.2mm_M3
HLCD_1, HLCD_2, HLCD_3, HLCD_4: M3 Entretoise LCD; MountingHole_3.2mm_M3
J_DIN: CABLE MONTURE; SolderWire-0.5sqmm_1x04_P4.8mm_D0.9mm_OD2.3mm
J_GROVE: Grove I2C Aux; PinHeader_1x04_P2.54mm_Vertical
J_LCD_I2C: LCD Backpack I2C; PinHeader_1x04_P2.54mm_Vertical
Q_SCL: BSS138; SOT-23_Handsoldering
Q_SDA: BSS138; SOT-23_Handsoldering
R_SCL_3V3, R_SCL_5V: 10k; R_Axial_DIN0204_L3.6mm_D1.6mm_P2.54mm_Vertical
R_SDA_3V3, R_SDA_5V: 10k; R_Axial_DIN0204_L3.6mm_D1.6mm_P2.54mm_Vertical
SW_DOWN: BAS; SW_PUSH_6mm
SW_ENTER: ENTER / OK; SW_PUSH_6mm
SW_LEFT: GAUCHE; SW_PUSH_6mm
SW_RIGHT: DROITE; SW_PUSH_6mm
SW_UP: HAUT; SW_PUSH_6mm
U1: Teensy 4.1; Teensy41

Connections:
+3V3: Q_SCL.1, Q_SDA.1, R_SCL_3V3.1, R_SDA_3V3.1, U1.46
+5V: J_DIN.2, J_GROVE.3, J_LCD_I2C.2, R_SCL_5V.1, R_SDA_5V.1, U1.48
BTN_DOWN: SW_DOWN.2, U1.9
BTN_ENTER: SW_ENTER.2, U1.12
BTN_LEFT: SW_LEFT.2, U1.10
BTN_RIGHT: SW_RIGHT.2, U1.11
BTN_UP: SW_UP.2, U1.8
GND: J_DIN.1, J_GROVE.4, J_LCD_I2C.1, SW_DOWN.1, SW_ENTER.1, SW_LEFT.1, SW_RIGHT.1, SW_UP.1, U1.1, U1.47
I2C_SCL: J_GROVE.1, J_LCD_I2C.4, Q_SCL.3, R_SCL_5V.2
I2C_SCL_3V3: Q_SCL.2, R_SCL_3V3.2, U1.41
I2C_SDA: J_GROVE.2, J_LCD_I2C.3, Q_SDA.3, R_SDA_5V.2
I2C_SDA_3V3: Q_SDA.2, R_SDA_3V3.2, U1.40
RAQ_RX: J_DIN.4, U1.2
RAQ_TX: J_DIN.3, U1.3

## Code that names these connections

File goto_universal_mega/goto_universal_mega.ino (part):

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 * Cablage :
 * - Moteur AZ  : Step Pin 2, Dir Pin 3
 * - Moteur ALT : Step Pin 5, Dir Pin 6
 * - Buzzer     : Pin 11
 * - Raquette   : Serial3 (Pin 14 TX, Pin 15 RX) @ 38400 baud (Connecteur DIN 4 broches)
 * - Module GPS : Serial2 (Pin 16 TX, Pin 17 RX) @ 9600 baud
 */
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static double         maxSlewRate   = DEFAULT_SLEW_RATE;

// === BROCHES ===
#define AZ_STEP   2
#define AZ_DIR    3
#define AZ_EN     4
#define BUZZER_PIN 49
#define BUZZ_FREQ  2000
#define ALT_STEP  5
#define ALT_DIR   6
#define ALT_EN    7

#define DEROT_STEP 8
#define DEROT_DIR  9
#define DEROT_EN   10

#define FOCUS_STEP 11
#define FOCUS_DIR  12
#define FOCUS_EN   13

// === LIMITES ===
#define ALT_MIN  -1.0
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      else if(cmd[3] == '1') { buzzerEnabled = true; saveStateToEEPROM(); }
      else if(cmd[3] == 'p') {
        if(buzzerEnabled) {
          tone(BUZZER_PIN, BUZZ_FREQ);
          delay(80);
          noTone(BUZZER_PIN);
          digitalWrite(BUZZER_PIN, LOW);
        }
      }
    }
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
void playStartupMelody() {
  if(!buzzerEnabled) return;
  tone(BUZZER_PIN, NOTE_C5); delay(150);
  tone(BUZZER_PIN, NOTE_E5); delay(150);
  tone(BUZZER_PIN, NOTE_G5); delay(150);
  tone(BUZZER_PIN, NOTE_C6); delay(300);
  noTone(BUZZER_PIN);
}

void playArrivalMelody() {
  if(!buzzerEnabled) return;
  tone(BUZZER_PIN, NOTE_G5); delay(150);
  tone(BUZZER_PIN, NOTE_C6); delay(300);
  noTone(BUZZER_PIN);
}

static bool firstCmdReceived  = false;
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      alarmBuzzActive = true;
      alarmBuzzState = true;
      alarmBuzzNext = now + 150;
      tone(BUZZER_PIN, 1500);
    } else if (now >= alarmBuzzNext) {
      if (alarmBuzzState) {
        noTone(BUZZER_PIN);
        digitalWrite(BUZZER_PIN, LOW);
        alarmBuzzState = false;
        alarmBuzzNext = now + 150;
      } else {
        tone(BUZZER_PIN, 1500);
        alarmBuzzState = true;
        alarmBuzzNext = now + 150;
      }
    }
    return;
  } else if (alarmBuzzActive) {
    noTone(BUZZER_PIN);
    digitalWrite(BUZZER_PIN, LOW);
    alarmBuzzActive = false;
  }
  
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
  if (tryingForbiddenMove && buzzerEnabled) {
    if (!limitBuzzActive) {
      tone(BUZZER_PIN, BUZZ_FREQ);
      limitBuzzActive = true;
    }
    return;
  } else if (limitBuzzActive) {
    noTone(BUZZER_PIN);
    digitalWrite(BUZZER_PIN, LOW);
    limitBuzzActive = false;
  }

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    if(now < connectBeepNext) return;
    switch(connectBeepStep){
      case 0: case 2: case 4:
        tone(BUZZER_PIN, BUZZ_FREQ);
        connectBeepNext = now + 80; break;
      case 1: case 3:
        noTone(BUZZER_PIN);
        connectBeepNext = now + 120; break;
      case 5:
        noTone(BUZZER_PIN);
        digitalWrite(BUZZER_PIN, LOW);
        connectBeepActive = false; return;
    }
    connectBeepStep++;
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    if(now < gpsFixBeepNext) return;
    switch(gpsFixBeepStep){
      case 0:
        tone(BUZZER_PIN, 261); gpsFixBeepNext = now + 200; break; // C4
      case 1:
        tone(BUZZER_PIN, 329); gpsFixBeepNext = now + 200; break; // E4
      case 2:
        tone(BUZZER_PIN, 392); gpsFixBeepNext = now + 400; break; // G4
      case 3:
        noTone(BUZZER_PIN);
        digitalWrite(BUZZER_PIN, LOW);
        gpsFixBeepActive = false; return;
    }
    gpsFixBeepStep++;
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  if(shouldBuzz && !slewBuzzActive){
    slewBuzzActive = true; slewBuzzState  = true;
    slewBuzzNext   = now + 80;
    tone(BUZZER_PIN, BUZZ_FREQ); return;
  }
  if(!shouldBuzz && slewBuzzActive){
    slewBuzzActive = false; slewBuzzState  = false;
    noTone(BUZZER_PIN);
    digitalWrite(BUZZER_PIN, LOW); return;
  }
  if(!slewBuzzActive) return;
  if(now < slewBuzzNext) return;
  if(slewBuzzState){
    noTone(BUZZER_PIN);
    slewBuzzState = false; slewBuzzNext  = now + 920;
  } else {
    tone(BUZZER_PIN, BUZZ_FREQ);
    slewBuzzState = true;  slewBuzzNext  = now + 80;
  }
}
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  Serial3.begin(38400);                   
  Serial2.begin(9600);   // [ADD] Initialisation du port GPS

  pinMode(AZ_STEP,OUTPUT); pinMode(AZ_DIR,OUTPUT); pinMode(AZ_EN,OUTPUT);
  pinMode(ALT_STEP,OUTPUT);pinMode(ALT_DIR,OUTPUT);pinMode(ALT_EN,OUTPUT);
  pinMode(DEROT_STEP,OUTPUT); pinMode(DEROT_DIR,OUTPUT); pinMode(DEROT_EN,OUTPUT);
  pinMode(FOCUS_STEP,OUTPUT); pinMode(FOCUS_DIR,OUTPUT); pinMode(FOCUS_EN,OUTPUT);
  digitalWrite(DEROT_EN, HIGH);
  digitalWrite(FOCUS_EN, HIGH);
  digitalWrite(AZ_STEP,LOW); digitalWrite(ALT_STEP,LOW);
  enableMotors(false);
  pinMode(LED_BUILTIN,OUTPUT);
  digitalWrite(LED_BUILTIN,HIGH); delay(300); digitalWrite(LED_BUILTIN,LOW);
  pinMode(BUZZER_PIN,OUTPUT);
  digitalWrite(BUZZER_PIN,LOW);
  azPos=0; altPos=0;
  loadStateFromEEPROM();
  if (!parked) {
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
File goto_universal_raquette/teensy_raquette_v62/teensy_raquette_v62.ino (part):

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// SECTION 1 : CONFIGURATION
// ============================================================
#define LCD_ADDR   0x27
#define BTN_UP      6
#define BTN_DOWN    7
#define BTN_LEFT    8
#define BTN_RIGHT   9
#define BTN_ENTER  10

#define MEGA_BAUD         38400
#define POLL_INTERVAL_MS   250    
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// ============================================================
// SECTION 5 : BOUTONS
// ============================================================
const uint8_t BTN_PINS[5] = {BTN_UP,BTN_DOWN,BTN_LEFT,BTN_RIGHT,BTN_ENTER};
#define BTN_IDX_UP    0
#define BTN_IDX_DOWN  1
#define BTN_IDX_LEFT  2
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
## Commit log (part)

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2026-06-23 Initial commit of GotoUniversal
2026-06-23 Add firmware flashing feature to configurator and fix Teensy compilation
2026-06-23 Remove Saint-Jacques default observatory location and use generic 0.0/0.0 coordinates
2026-06-23 Make documentation and main application header generic by removing Dobson 800mm specific references
2026-06-23 Simplify sketch header comment to clean developer style
2026-06-23 Add GNU GPL v3 license file and update README
2026-06-23 Add Installation and User Guide to README
2026-06-23 Add quick wiring diagram to README
2026-06-23 Add compatible hardware list to README
2026-06-27 UI: Adaptation de la raquette virtuelle et physique pour afficheur Grove I2C 16x2 et ajout d'animation GoTo
2026-06-27 Fix: Ajout effectif de la synchronisation sur la raquette Python
2026-06-27 UI: Synchronisation finale des menus (Type Monture) entre raquettes
2026-06-27 Fix: Crash au lancement de la raquette
2026-06-27 Feat: Ajout Ratios AZ/ALT et filtrage des etoiles visibles
2026-06-27 UI: Affichage dynamique Ratio AZ/ALT ou RA/DEC selon type monture + Fix affichage Sync
2026-06-27 Feat: Propose etoile auto pour alignement et asterisques de visibilite
2026-06-27 Feat: Complete le workflow d'alignement a 1 etoile avec la phase de centrage
2026-06-27 UI: Supprime <=RET inutile dans la phase d'alignement
2026-06-27 Fix: La liste des objets etait ecrasee par l'affichage LCD, empechant les asterisques d'apparaitre
2026-06-27 Feat: Securite empêchant un GOTO ou une synchronisation sur un objet sous l'horizon
2026-06-27 Feat: Portage alignement et securite horizon vers la Teensy
2026-06-27 Feat: Integration du support ecran Grove 104020112 I2C RGB
2026-06-27 Fix: Plantage de la raquette virtuelle avec les couleurs LCD
2026-06-27 Fix: Annulation de l'ecran RVB (l'ecran physique est monochrome rouge) et ajout animation flocon
2026-06-27 Doc: Ajout du cablage de la Teensy et de l'ecran LCD I2C
2026-06-27 Feat: Parametrage de la position de Parking sur mesure via le Configurateur et l'Arduino Mega
2026-06-27 Feat: Interface GUI du Configurateur pour la position de Parking sur mesure
2026-06-27 Fix: Plantage du configurateur (traductions manquantes)
2026-06-27 Style: Retrait des emojis pour un aspect plus professionnel
2026-06-27 Style: Retrait de la fusee sur le bouton de flash
2026-06-27 Feat/Fix: Mise a jour auto de la position parking selon le type de monture
2026-06-27 Feat: Changement des labels Altitude/Azimut vers DEC/RA pour la position parking en mode Equatorial
2026-06-28 Add parking animation to virtual hand controller and teensy
2026-06-28 Add GitHub update button to configurator UI
2026-06-28 Rename flash buttons to update buttons and integrate git pull
2026-06-28 Change update button text to 'Mettre à jour & Flasher'
2026-06-28 Fix UI freeze during flash by running subprocess in a thread
2026-06-28 Clean up header block
2026-06-28 Add author name to python files
2026-06-28 Add author name to INO headers
2026-06-28 Add author signature to GUI footer
2026-06-28 Move author signature to bottom right corner
2026-06-28 Remove redundant custom Win95 title bars
